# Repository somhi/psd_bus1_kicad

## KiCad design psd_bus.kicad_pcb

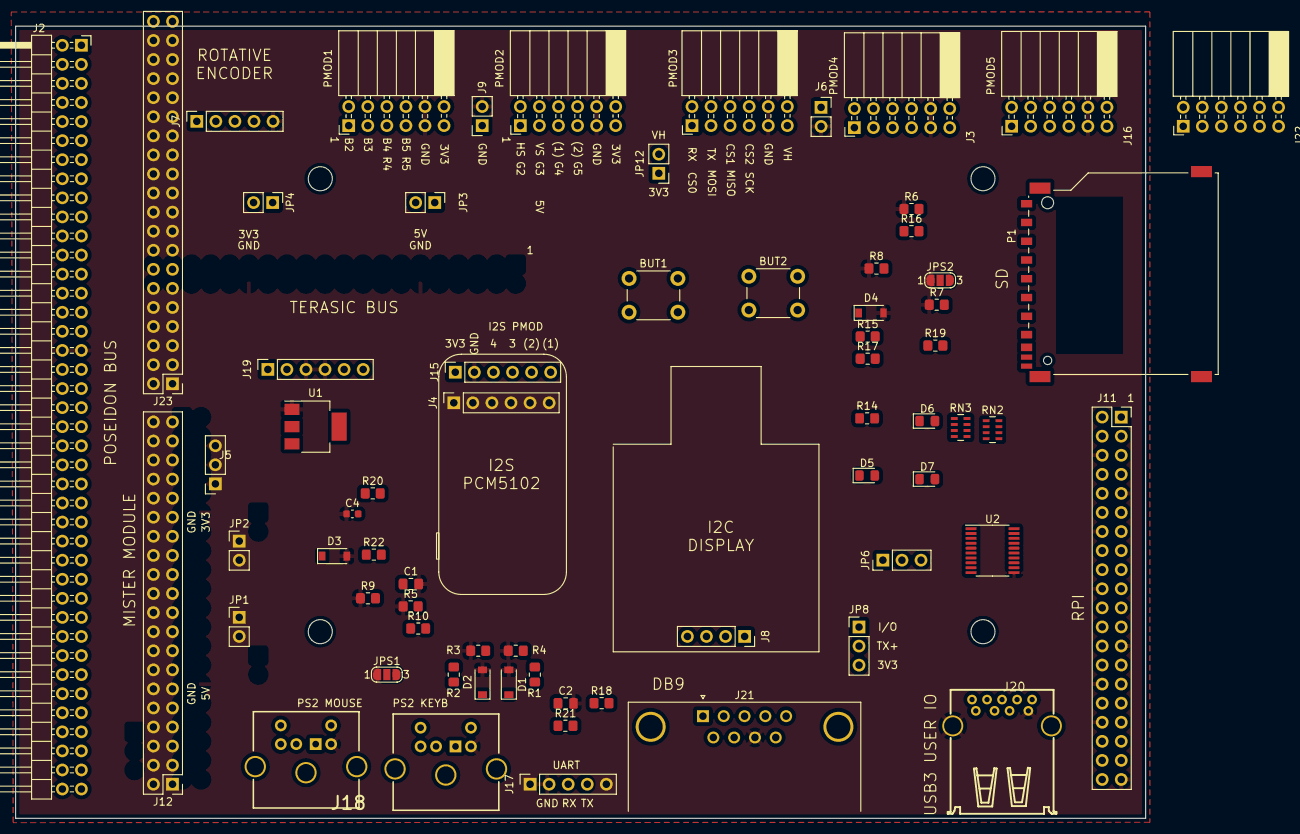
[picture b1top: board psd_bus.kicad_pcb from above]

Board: 2 copper layers, 150.5 x 105.5 mm, 72 parts (0 on the bottom side), 112 nets, no tracks yet.

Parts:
BUT1, BUT2: SW_DIP_x01; SW_PUSH_6mm_H5mm
C1: 1uF; C_0805_2012Metric_Pad1.18x1.45mm_HandSolder
C2: 10uF; C_0805_2012Metric_Pad1.18x1.45mm_HandSolder
C4: 100nF; C_0603_1608Metric
D1, D2, D3, D4: BZT52C3V9; D_SOD-123
D5, D6, D7: LED; LED_0805_2012Metric_Pad1.15x1.40mm_HandSolder
H1, H2, H3, H4: MountingHole; MountingHole_3.2mm_M3
J1: PMOD1; PMOD_Female_Horizontal_2
J2: Conn_02x40_Odd_Even; PinHeader_2x40_P2.54mm_Horizontal
J3: PMOD4; PMOD_Female_Horizontal_2
J4, J15: Conn_01x06; PCM5102
J5: Conn_01x03; PinSocket_1x03_P2.54mm_Vertical
J6, J9: Conn_01x02; PinSocket_1x02_P2.54mm_Vertical
J7, J17: Conn_01x05; PinSocket_1x05_P2.54mm_Vertical
J8: Conn_01x04; I2C_DISPLAY_MULTI2
J10: PMOD2; PMOD_Female_Horizontal_2
J11: RASPBERRYPI_BPLUS_BONNETNODIM; PinSocket_2x20_P2.54mm_Vertical
J12, J23: Conn_02x20_Odd_Even; PinHeader_2x20_P2.54mm_Vertical
J13: PMOD3; PMOD_Female_Horizontal_2
J14, J18: DINC_MIN_TM_6_1; DINC_MIN_TM_6_1PRIMARY
J16, J22: PMOD5; PMOD_Female_Horizontal_2
J19: Conn_02x06_Odd_Even; PinSocket_1x06_P2.54mm_Vertical
J20: USB3_A; USB-3.0-TH_C69073
J21: DB9_Male_MountingHoles; DSUB-9_Male_Horizontal_P2.77x2.84mm_EdgePinOffset9.90mm_Hou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
JP1, JP2, JP3, JP4, JP12: Conn_01x02; PinHeader_1x02_P2.54mm_Vertical
JP6, JP8: Conn_01x03; PinHeader_1x03_P2.54mm_Vertical
JPS1, JPS2: SolderJumper_3_Open; SolderJumper-3_P1.3mm_Open_RoundedPad1.0x1.5mm_NumberLabels
P1: MEM1055-00-280-01-B; SD_TE_2041021
R1, R2, R14, R15, R16, R17, R18, R19, R20, R21, R22: 510; R_0805_2012Metric_Pad1.20x1.40mm_HandSolder
R3, R4: DNI 4k7; R_0805_2012Metric_Pad1.20x1.40mm_HandSolder
R5, R6: 1k; R_0805_2012Metric_Pad1.20x1.40mm_HandSolder
R7, R8, R9: 220; R_0805_2012Metric_Pad1.20x1.40mm_HandSolder
R10: 200; R_0805_2012Metric_Pad1.20x1.40mm_HandSolder
RN2, RN3: 20K; R_Array_Concave_4x0603
U1: LM1117-3.3; SOT-223-3_TabPin2
U2: TXS0108EPWR; TSSOP-20_4.4x6.5mm_P0.65mm

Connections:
+3V3: C2.1, J1.6, J1.12, J4.6, J7.4, J10.6, J10.12, J15.6, J16.6, J16.12, J22.6, J22.12, JP2.1, JP4.1, JP6.3, JP8.3, JP12.1, JPS1.3 (B), JPS2.3 (B), RN2.1, RN2.2, RN2.3, RN2.4, RN3.1, RN3.2, RN3.3, RN3.4, U1.2 (VO), U2.2 (VCCA), U2.10 (OE)
+5V: C1.1, J2.35, J2.36, J6.1, J9.1, J14.4, J18.4, J19.1, J19.2, JP1.1, JP3.1, JP6.1, U1.3 (VI)
/+3.3V: J19.5, J19.6
/+JOY_PWR: J20.1 (VBUS), J21.5, JP6.2, U2.19 (VCCB)
/D+: J20.3 (D+), J21.2, R20.2
/D-: J20.2 (D-), J21.1, R22.2
/DISPLAY_PS1: J8.1, JPS2.2 (C)
/DISPLAY_PS2: J8.2, JPS1.2 (C)
/DRAIN: J20.7 (DRAIN), J21.4, R17.2
/IO_1: J1.1, J2.1, J23.39
/IO_2: J1.2, J2.2, J23.40
/IO_3: J1.3, J2.3, J23.37
/IO_4: J1.4, J2.4, J23.38
/IO_5: J1.7, J2.5, J23.35
/IO_6: J1.8, J2.6, J23.36
/IO_7: J1.9, J2.7, J23.33
/IO_8: J1.10, J2.8, J23.34
/IO_9: J2.9, J10.1, J23.31
/IO_10: J2.10, J10.2, J23.32
/IO_11: J2.11, J10.3, J23.27
/IO_12: J2.12, J10.4, J23.28
/IO_13: J2.13, J10.7, J23.25
/IO_14: J2.14, J10.8, J23.26
/IO_15: J2.15, J10.9, J23.23
/IO_16: J2.16, J10.10, J23.24
/IO_17: J2.17, J13.1, J23.21
/IO_18: J2.18, J13.2, J23.22
/IO_19: J2.19, J13.3, J23.19
/IO_20: J2.20, J13.4, J23.20
/IO_21: J2.21, J13.7, J23.17
/IO_22: J2.22, J13.8, J23.18
/IO_23: J2.23, J13.9, J23.15
/IO_24: J2.24, J13.10, J23.16
/IO_25: J2.25, J3.1, J23.13
/IO_26: J2.26, J3.2, J23.14
/IO_27: J2.27, J3.3, J23.9
/IO_28: J2.28, J3.4, J23.10
/IO_29: J2.29, J3.7, J23.7
/IO_30: J2.30, J3.8, J23.8
/IO_31: J2.31, J3.9, J23.5
/IO_32: J2.32, J3.10, J23.6
/IO_37: J2.37, J22.1, J23.3
/IO_38: J2.38, J22.2, J23.4
/IO_39: J2.39, J22.3, J23.1
/IO_40: J2.40, J22.4, J23.2
/IO_41: J2.41, J22.7
/IO_42: J2.42, J5.1, J22.8
/IO_43: J2.43, J5.2, J22.9
/IO_44: J2.44, J5.3, J22.10
/IO_45: J2.45, J11.21 (SPI_MISO), J12.39, J16.3
/IO_46: J2.46, J11.23 (SPI_SCLK), J12.40, J16.4
/IO_47: J2.47, J11.10 (RXD), J11.24 (#SPI_CE0), J12.37, J16.1
/IO_48: J2.48, J11.8 (TXD), J11.19 (SPI_MOSI), J12.38, J16.2
/IO_49: BUT1.2, J2.49, J11.11 (GPIO17), J11.18 (GPIO24), J12.35, J16.9
/IO_50: BUT2.2, J2.50, J11.13 (GPIO27), J12.36
/IO_51: D7.2 (A), J2.51, J4.4, J12.33, J15.1
/IO_52: J2.52, J7.3, J11.7 (GPIO4), J11.22 (GPIO25), J12.34, J16.10
/IO_53: D5.2 (A), J2.53, J12.31, J17.4
/IO_54: D6.2 (A), J2.54, J7.1, J11.15 (GPIO22), J12.32, J16.7, J17.5
/IO_55: J2.55, J8.3, J11.5 (SCL), J12.27
/IO_56: J2.56, J8.4, J11.3 (SDA), J12.28
/IO_57: J2.57, J4.1, J11.12 (GPIO18), J12.25, J15.2
/IO_58: J2.58, J4.2, J11.40 (GPIO21), J12.26, J15.3
/IO_59: J2.59, J7.2, J11.16 (GPIO23), J12.23, J16.8
/IO_60: J2.60, J4.3, J11.35 (GPIO19), J12.24, J15.4
/IO_61: J2.61, J12.21, RN3.6
/IO_62: J2.62, J12.22, R10.1, RN2.6
/IO_63: J2.63, J12.19, RN2.7
/IO_64: J2.64, J12.20, RN3.5
/IO_65: J2.65, J12.17, RN2.5
/IO_66: J2.66, J12.18, RN2.8
/IO_67: J2.67, J12.15, U2.6 (A5)
/IO_68: J2.68, J12.16, RN3.7
/IO_69: J2.69, J12.13, U2.5 (A4)
/IO_70: J2.70, J12.14, U2.4 (A3)
/IO_71: J2.71, J12.9, U2.9 (A8)
/IO_72: J2.72, J12.10, U2.7 (A6)
/IO_73: J2.73, J12.7, U2.3 (A2)
/IO_74: J2.74, J12.8, U2.8 (A7)
/IO_75: J2.75, J12.5, J17.2
/IO_76: J2.76, J12.6, J17.3
/IO_77: D3.1 (K), J2.77, J12.3, R14.1
/IO_78: D4.1 (K), J2.78, J12.4, R15.1
/IO_79: D1.1 (K), J2.79, J12.1, R1.1
/IO_80: D2.1 (K), J2.80, J12.2, R2.1
/RX+: J20.6 (SSRX+), J21.7, R19.2
/RX-: J20.5 (SSRX-), J21.3, R18.2
/TX+: J20.9 (SSTX+), JP8.2
/TX+b: J21.9, JP8.1, R16.2
/TX-: J20.8 (SSTX-), J21.6, R21.2
/VH_PMOD: J3.6, J3.12, J13.6, J13.12, JP12.2
GND: C1.2, C2.2, C4.1, D1.2 (A), D2.2 (A), D3.2 (A), D4.2 (A), J1.5, J1.11, J2.33, J2.34, J3.5, J3.11, J4.5, J6.2, J7.5, J9.2, J10.5, J10.11, J11.6 (GND), J11.9 (GND@4), J11.14 (GND@1), J11.20 (GND@2), J11.25 (GND@3), J11.30 (GND@6), J11.34 (GND@7), J11.39 (GND@5), J12.12, J12.30, J13.5, J13.11, J14.3, J15.5, J16.5, J16.11, J17.1, J18.3, J19.3, J19.4, J20.4 (GND), J20.10 (SHIELD), J21.8, J22.5, J22.11, J23.12, J23.30, JPS1.1 (A), JPS2.1 (A), R3.2, R4.2, R5.1, R6.1, R7.1, R8.1, R9.1, U1.1 (GND), U2.11 (GND)
unnamed: BUT1.1, R5.2
unnamed: BUT2.1, R6.2
unnamed: D5.1 (K), R7.2
unnamed: D6.1 (K), R8.2
unnamed: D7.1 (K), R9.2
unnamed: J12.11, JP3.2
unnamed: J12.29, JP4.2
unnamed: J14.1, R2.2, R3.1
unnamed: J14.5, R1.2, R4.1
unnamed: J18.1, R15.2
unnamed: J18.5, R14.2
unnamed: J23.11, JP1.2
unnamed: J23.29, JP2.2
unnamed: R16.1, U2.18 (B2)
unnamed: R17.1, U2.17 (B3)
unnamed: R18.1, U2.16 (B4)
unnamed: R19.1, U2.15 (B5)
unnamed: R20.1, U2.14 (B6)
unnamed: R21.1, U2.13 (B7)
unnamed: R22.1, U2.12 (B8)

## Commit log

2024-01-17 preliminary distribution on pcb
2024-01-26 updated WIP
